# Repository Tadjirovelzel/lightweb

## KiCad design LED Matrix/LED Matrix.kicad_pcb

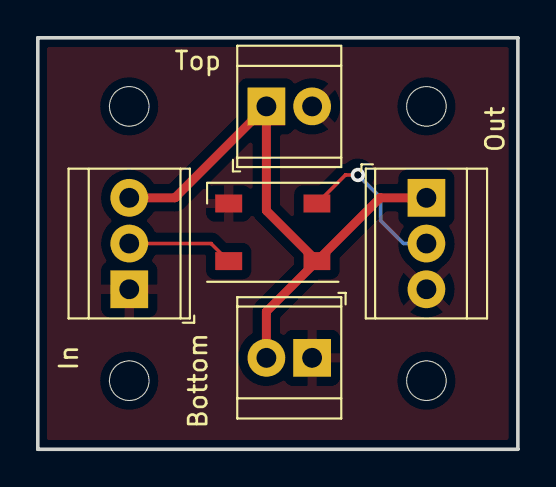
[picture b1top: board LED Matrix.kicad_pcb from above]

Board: 2 copper layers, 26.7 x 22.9 mm, 5 parts (0 on the bottom side), 4 nets.

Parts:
Bottom: Screw_Terminal_01x02; TerminalBlock_TE_282834-2_1x02_P2.54mm_Horizontal
In: Screw_Terminal_01x03; TerminalBlock_TE_282834-3_1x03_P2.54mm_Horizontal
Out: Screw_Terminal_01x03; TerminalBlock_TE_282834-3_1x03_P2.54mm_Horizontal
Pix1: SK6812; LED_SK6812_PLCC4_5.0x5.0mm_P3.2mm
Top: Screw_Terminal_01x02; TerminalBlock_TE_282834-2_1x02_P2.54mm_Horizontal

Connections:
/PixelSide/5V: Bottom.2, In.3, Out.1, Pix1.3 (VDD), Top.1
/PixelSide/Data: In.2, Pix1.2 (DIN)
/PixelSide/gnd: Bottom.1, In.1, Out.3, Pix1.1 (VSS), Top.2
unnamed: Out.2, Pix1.4 (DOUT)

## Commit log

2022-11-13 Birth of Kicad
2022-11-13 save
